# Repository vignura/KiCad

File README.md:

# KiCad
PCB projects with KiCad

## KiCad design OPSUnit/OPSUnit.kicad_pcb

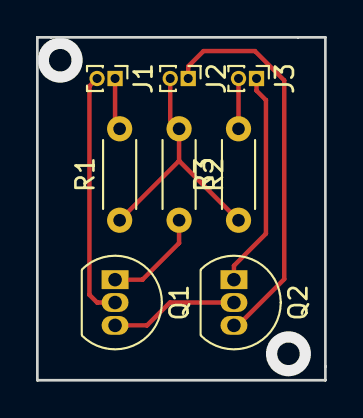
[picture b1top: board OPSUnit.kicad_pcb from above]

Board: 2 copper layers, 16.0 x 19.0 mm, 8 parts (0 on the bottom side), 8 nets.

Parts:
J1, J2, J3: Conn_01x02_Male; PinHeader_1x02_P1.00mm_Vertical
Q1, Q2: BC547; TO-92_Inline
R1: 1M; R_Axial_DIN0204_L3.6mm_D1.6mm_P5.08mm_Horizontal
R2, R3: 1K; R_Axial_DIN0204_L3.6mm_D1.6mm_P5.08mm_Horizontal

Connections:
GND: J2.1, Q2.3
unnamed: J1.1, R1.2
unnamed: J1.2, Q1.2
unnamed: J2.2, R1.1, R2.1, R3.1
unnamed: J3.1, Q2.1
unnamed: J3.2, R3.2
unnamed: Q1.1, R2.2
unnamed: Q1.3, Q2.2

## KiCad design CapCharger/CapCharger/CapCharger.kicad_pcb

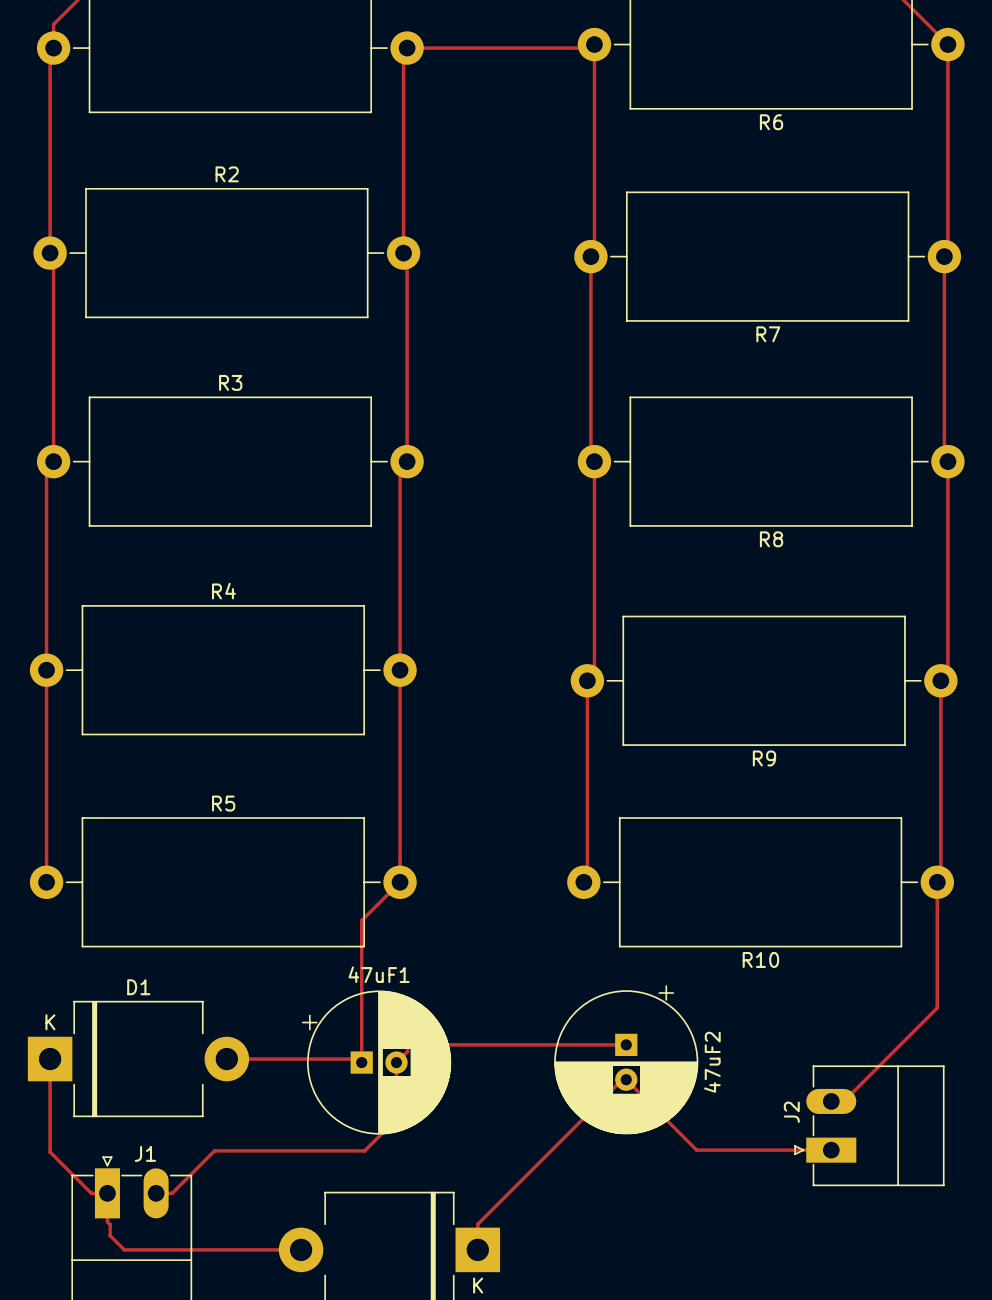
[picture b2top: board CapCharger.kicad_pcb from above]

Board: 2 copper layers, 16 parts (0 on the bottom side), 5 nets.

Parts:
47uF1, 47uF2: CAP; CP_Radial_D10.0mm_P2.50mm
D1, D2: DIODE; D_5KPW_P12.70mm_Horizontal
J1, J2: Conn_01x02_Male; PhoenixContact_MC_1,5_2-G-3.5_1x02_P3.50mm_Horizontal
R1, R2, R3, R4, R5, R6, R7, R8, R9, R10: 100K; R_Axial_DIN0922_L20.0mm_D9.0mm_P25.40mm_Horizontal

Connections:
unnamed: 47uF1.1, D1.2, R1.2, R2.2, R3.2, R4.2, R5.2, R6.2, R7.2, R8.2, R9.2, R10.2
unnamed: 47uF1.2, 47uF2.1, J1.2
unnamed: 47uF2.2, D2.1, J2.1
unnamed: D1.1, D2.2, J1.1
unnamed: J2.2, R1.1, R2.1, R3.1, R4.1, R5.1, R6.1, R7.1, R8.1, R9.1, R10.1
